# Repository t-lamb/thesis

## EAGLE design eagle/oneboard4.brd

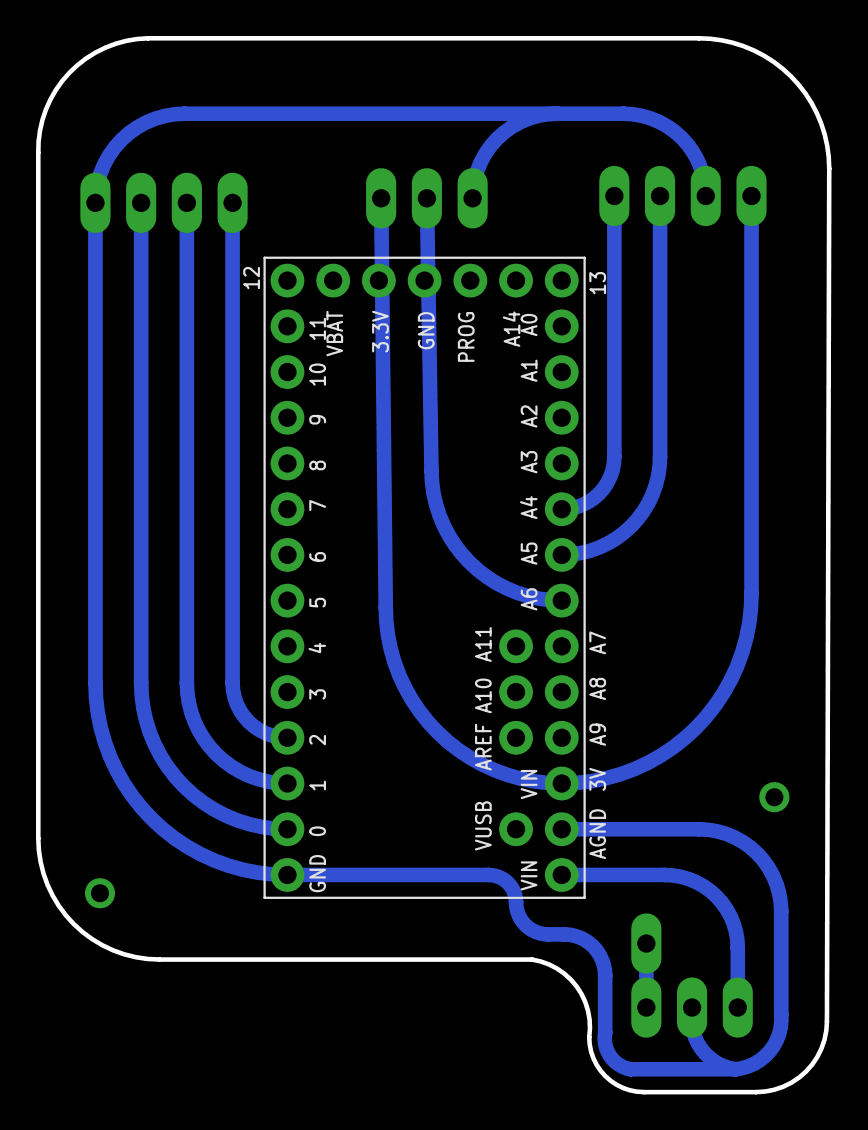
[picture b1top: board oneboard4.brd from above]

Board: 2 copper layers, 43.9 x 58.5 mm, 6 parts (1 on the bottom side), 10 nets.

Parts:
JP1: TEENSY-3.1SILK; TEENSY-3.1
U$1, U$2: HEADER-3
U$3: HEADER-1
U$4, U$5: HEADER-4

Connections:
GND: JP1.AGND, JP1.GND1, U$1.2, U$2.1, U$4.2, U$5.4
unnamed: JP1.1, U$5.2
unnamed: JP1.0, U$5.3
unnamed: JP1.2, U$5.1
unnamed: U$1.3, U$3.1
NEO: JP1.20, U$2.2
SCL: JP1.19, U$4.3
SDA: JP1.18, U$4.4
VCC: JP1.3V, U$2.3, U$4.1
VIN: JP1.VIN, U$1.1

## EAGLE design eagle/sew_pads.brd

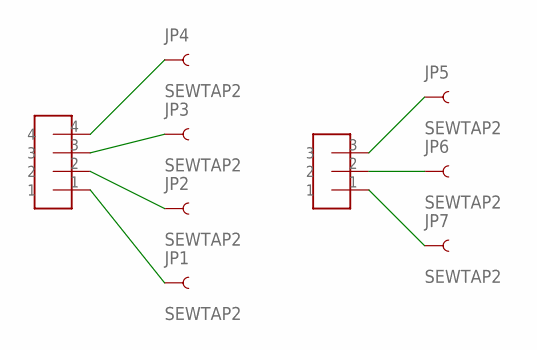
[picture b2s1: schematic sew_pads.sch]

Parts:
JP1, JP2, JP3, JP4, JP5, JP6, JP7: SEWTAP2; PETAL-LONG-2
U$1: HEADER-3
U$2: HEADER-4

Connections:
unnamed: JP4.1, U$2.4
unnamed: JP3.1, U$2.3
unnamed: JP2.1, U$2.2
unnamed: JP1.1, U$2.1
unnamed: JP5.1, U$1.3
unnamed: JP6.1, U$1.2
unnamed: JP7.1, U$1.1

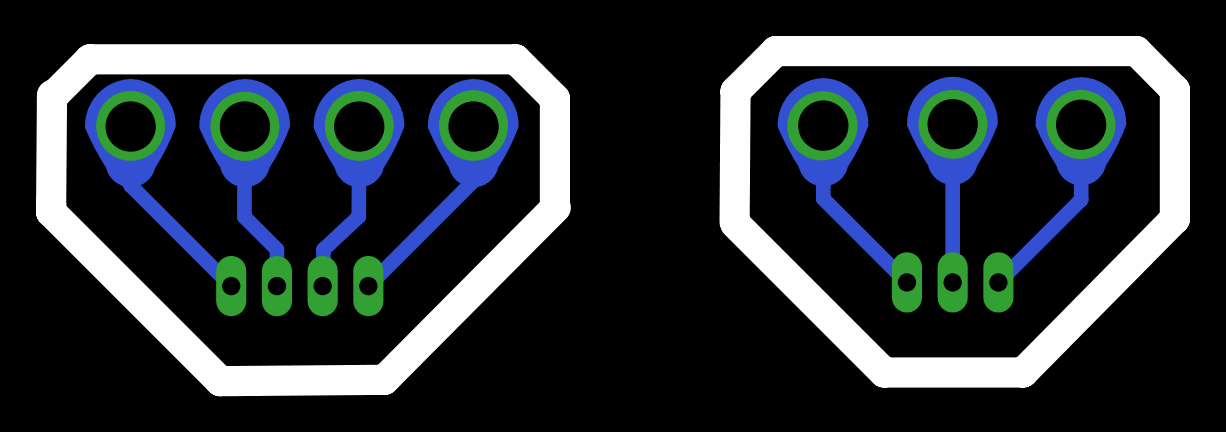
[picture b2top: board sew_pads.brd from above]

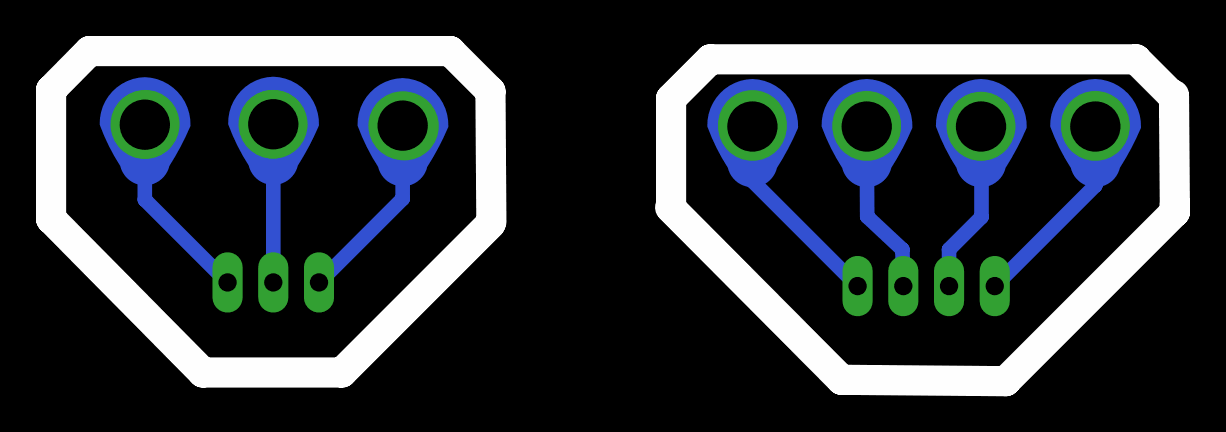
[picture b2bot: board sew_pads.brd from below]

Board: 2 copper layers, 62.4 x 18.3 mm, 9 parts (7 on the bottom side), 7 nets.

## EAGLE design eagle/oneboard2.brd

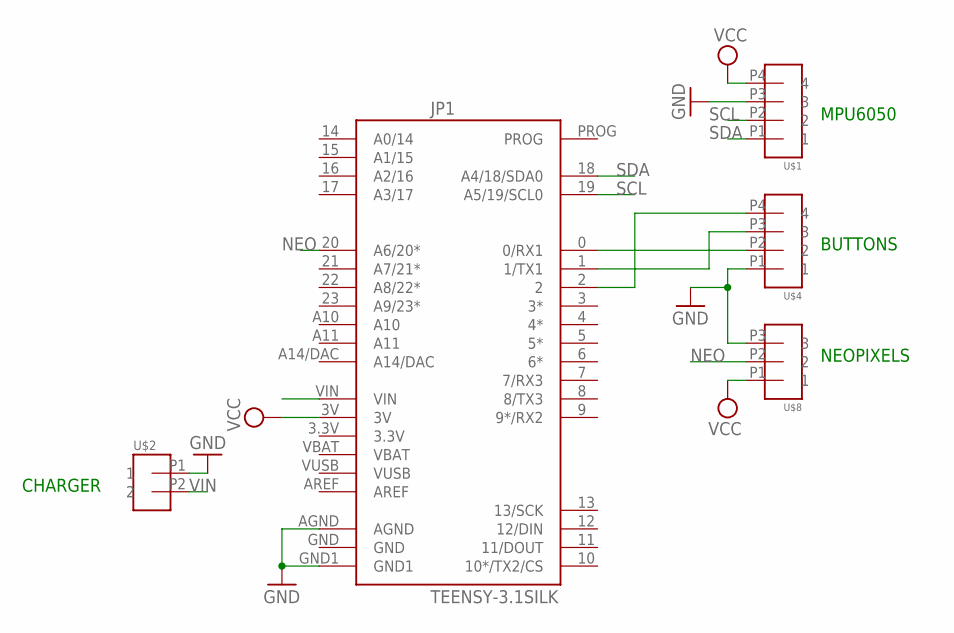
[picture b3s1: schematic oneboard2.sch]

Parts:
JP1: TEENSY-3.1SILK; TEENSY-3.1
U$1, U$4: PTSM0,4-HH-2,5-SMD-R44; M04_SMD_RIGHT
U$2: PTSM0,2-HH-2,5-SMD-R32; M02_SMD_RIGHT
U$8: PTSM0,3-HH-2,5-SMD-R44; M03_SMD_RIGHT

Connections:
GND: JP1.AGND, JP1.GND1, U$1.P3 (3), U$2.P1 (1), U$4.P1 (1), U$8.P3 (3)
unnamed: JP1.1 (1/TX1), U$4.P3 (3)
unnamed: JP1.0 (0/RX1), U$4.P2 (2)
unnamed: JP1.2, U$4.P4 (4)
NEO: JP1.20 (A6/20*), U$8.P2 (2)
SCL: JP1.19 (A5/19/SCL0), U$1.P2 (2)
SDA: JP1.18 (A4/18/SDA0), U$1.P1 (1)
VCC: JP1.3V, U$1.P4 (4), U$8.P1 (1)
VIN: JP1.VIN, U$2.P2 (2)

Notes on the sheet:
MPU6050
BUTTONS
NEOPIXELS
CHARGER

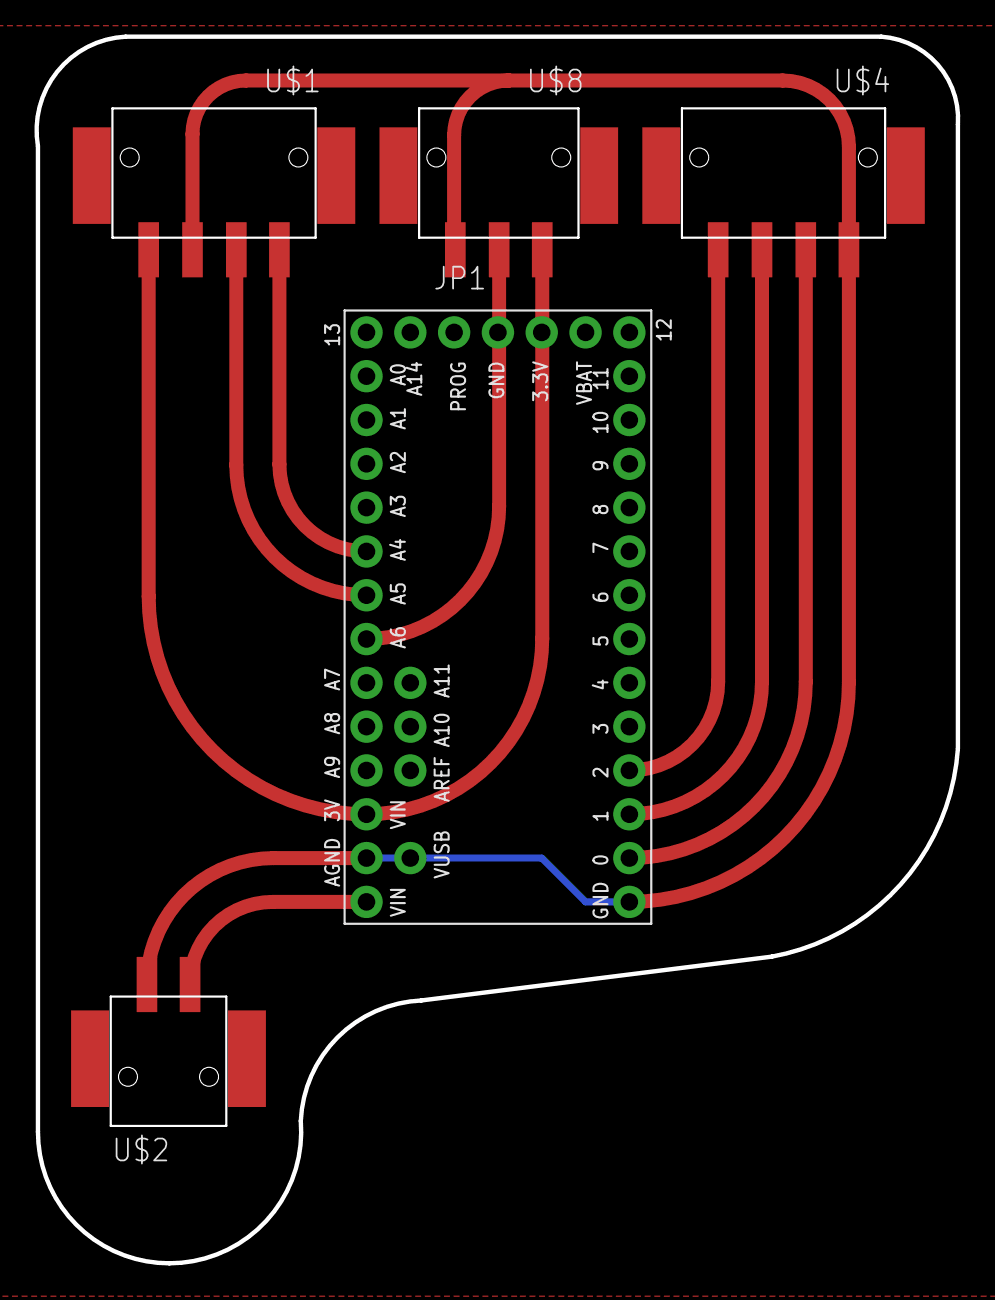
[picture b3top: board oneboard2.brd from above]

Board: 2 copper layers, 53.4 x 71.1 mm, 5 parts (0 on the bottom side), 9 nets.

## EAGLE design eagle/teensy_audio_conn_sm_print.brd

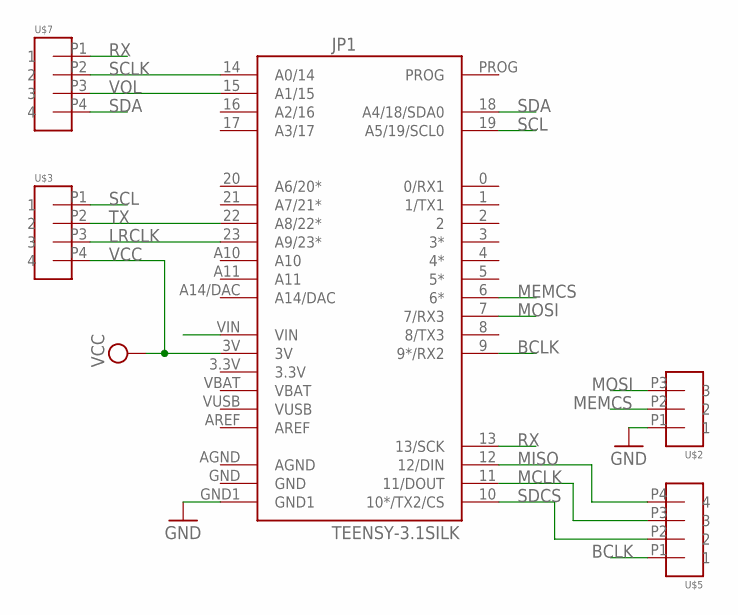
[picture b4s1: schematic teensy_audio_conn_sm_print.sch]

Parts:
JP1: TEENSY-3.1SILK; TEENSY-3.1
U$2: PTSM0,3-HH-2,5-SMD-R44; M03_SMD_RIGHT
U$3, U$5, U$7: PTSM0,4-HH-2,5-SMD-R44; M04_SMD_RIGHT

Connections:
BCLK: JP1.9 (9*/RX2), U$5.P1 (1)
GND: JP1.GND1, U$2.P1 (1)
LRCLK: JP1.23 (A9/23*), U$3.P3 (3)
MCLK: JP1.11 (11/DOUT), U$5.P3 (3)
MEMCS: JP1.6 (6*), U$2.P2 (2)
MISO: JP1.12 (12/DIN), U$5.P4 (4)
MOSI: JP1.7 (7/RX3), U$2.P3 (3)
RX: JP1.13 (13/SCK), U$7.P1 (1)
SCL: JP1.19 (A5/19/SCL0), U$3.P1 (1)
SCLK: JP1.14 (A0/14), U$7.P2 (2)
SDA: JP1.18 (A4/18/SDA0), U$7.P4 (4)
SDCS: JP1.10 (10*/TX2/CS), U$5.P2 (2)
TX: JP1.22 (A8/22*), U$3.P2 (2)
VCC: JP1.3V, U$3.P4 (4)
VIN: JP1.VIN
VOL: JP1.15 (A1/15), U$7.P3 (3)

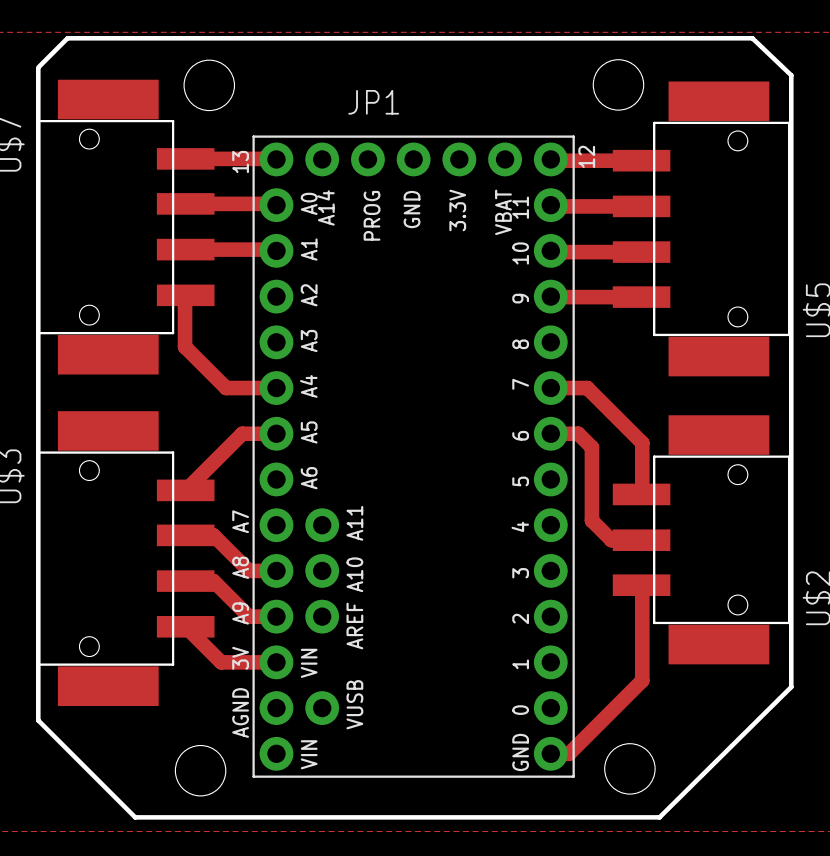
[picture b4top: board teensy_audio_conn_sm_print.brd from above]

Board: 2 copper layers, 41.8 x 43.3 mm, 5 parts (0 on the bottom side), 15 nets.

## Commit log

2016-04-03 with accel and gyro to midi
2016-04-03 added Arduino code
2016-04-03 max patch clean up
2016-04-03 accelgyro2 working
2016-04-04 mpu with teensy 3.1
2016-04-15 teensy working with audio board and accel
2016-04-23 added board files
2016-04-23 board for teensy and audio adaptor
2016-04-23 new round boards
2016-04-30 board updates
2016-04-30 added sew pads
2016-05-01 updated eagle board and arduino code
2016-05-13 fixed button presses
2016-05-18 reprogramming the buttons

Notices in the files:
parts and their libraries:
SparkFun-Boards: Licensing: Creative Commons ShareAlike 4.0 International - https://creativecommons.org/licenses/by-sa/4.0
